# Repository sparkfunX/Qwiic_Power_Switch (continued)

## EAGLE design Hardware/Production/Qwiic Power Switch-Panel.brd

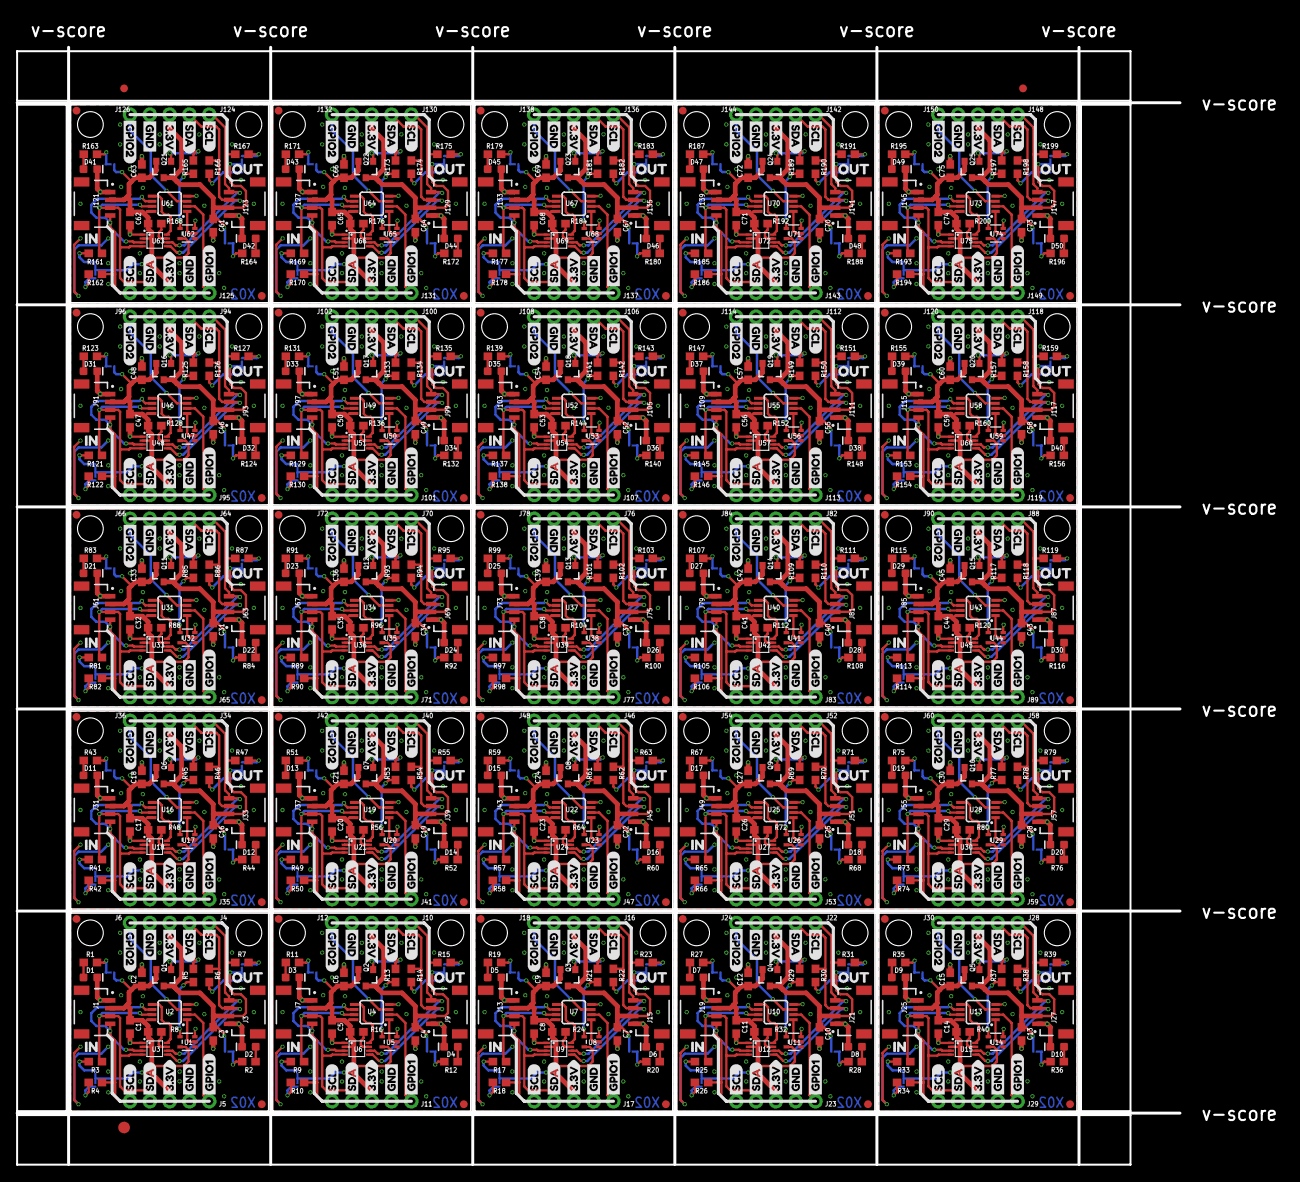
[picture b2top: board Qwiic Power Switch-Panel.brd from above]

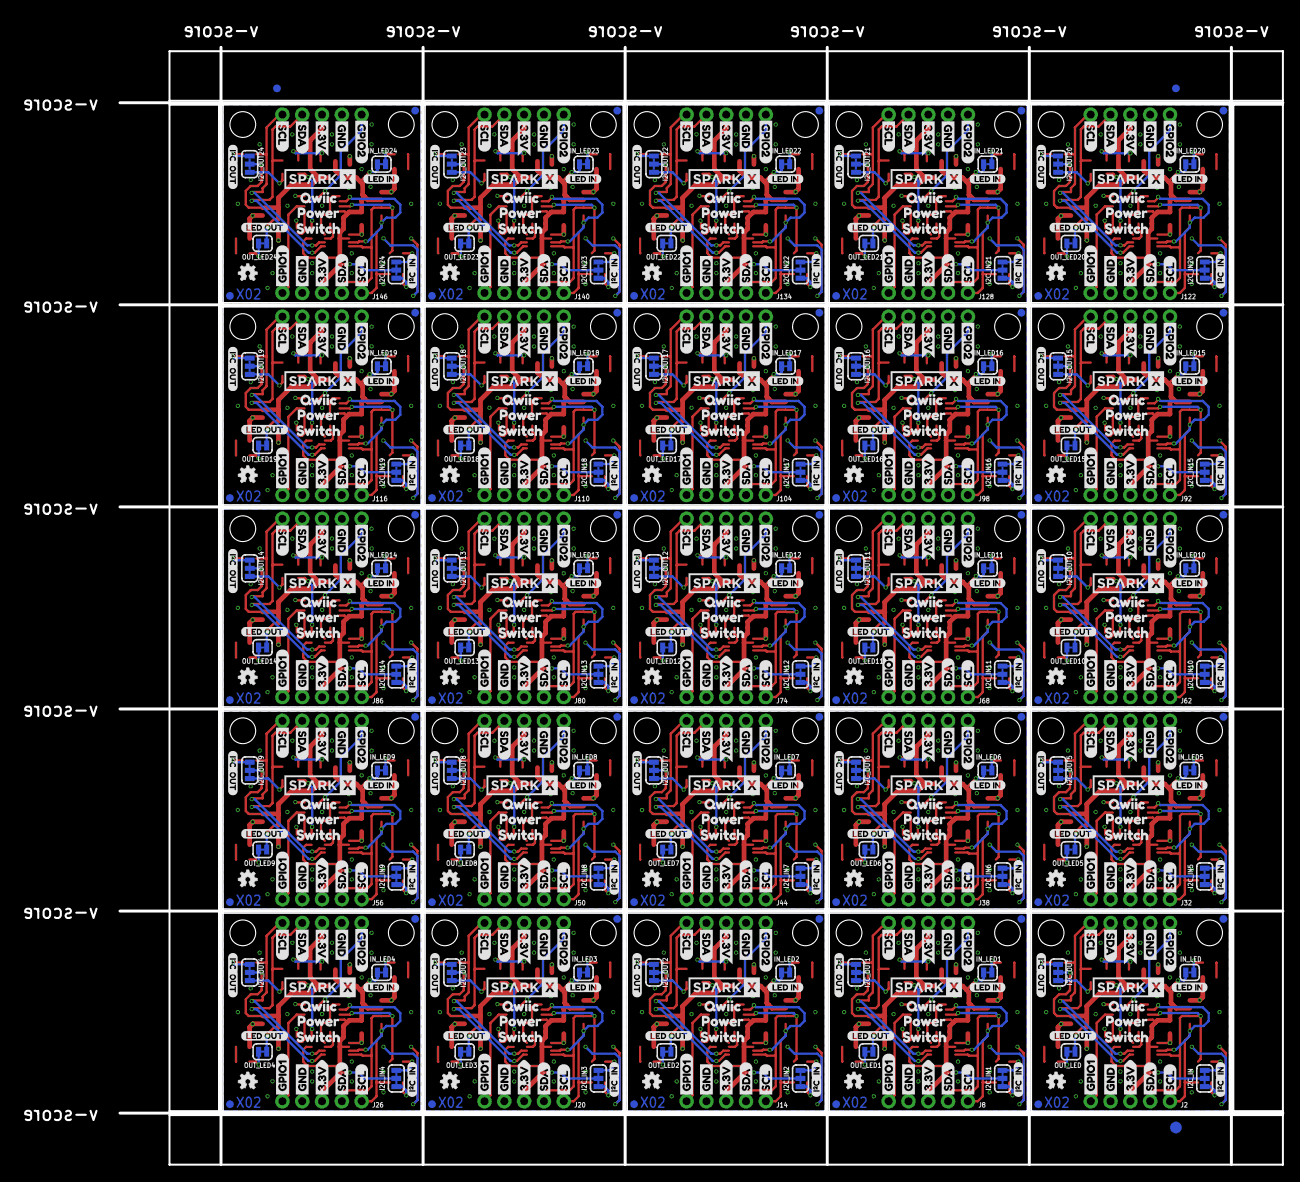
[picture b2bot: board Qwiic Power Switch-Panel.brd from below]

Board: 2 copper layers, 149.1 x 143.3 mm, 1656 parts (703 on the bottom side), 550 nets.

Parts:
C1, C3, C4, C5, C7, C8, C10, C11, C13, C14, C16, C17, C19, C20, C22, C23, C25, C26, C28, C29, C31, C32, C34, C35, C37, C38, C40, C41, C43, C44, C46, C47, C49, C50, C52, C53, C55, C56, C58, C59, C61, C62, C64, C65, C67, C68, C70, C71, C73, C74: 0.1uF; 0603
C2, C6, C9, C12, C15, C18, C21, C24, C27, C30, C33, C36, C39, C42, C45, C48, C51, C54, C57, C60, C63, C66, C69, C72, C75: 10uF; 0603
D1, D3, D5, D7, D9, D11, D13, D15, D17, D19, D21, D23, D25, D27, D29, D31, D33, D35, D37, D39, D41, D43, D45, D47, D49: RED; LED-0603
D2, D4, D6, D8, D10, D12, D14, D16, D18, D20, D22, D24, D26, D28, D30, D32, D34, D36, D38, D40, D42, D44, D46, D48, D50: GREEN; LED-0603
E$1, E$2, E$3, E$4: FIDUCIAL-1X2
E$5, E$6: FIDUCIAL-1.5X3
I2C_IN, I2C_IN1, I2C_IN2, I2C_IN3, I2C_IN4, I2C_IN5, I2C_IN6, I2C_IN7, I2C_IN8, I2C_IN9, I2C_IN10, I2C_IN11, I2C_IN12, I2C_IN13, I2C_IN14, I2C_IN15, I2C_IN16, I2C_IN17, I2C_IN18, I2C_IN19, I2C_IN20, I2C_IN21, I2C_IN22, I2C_IN23, I2C_IN24, I2C_OUT, I2C_OUT1, I2C_OUT2, I2C_OUT3, I2C_OUT4, I2C_OUT5, I2C_OUT6, I2C_OUT7, I2C_OUT8, I2C_OUT9, I2C_OUT10, I2C_OUT11, I2C_OUT12, I2C_OUT13, I2C_OUT14, I2C_OUT15, I2C_OUT16, I2C_OUT17, I2C_OUT18, I2C_OUT19, I2C_OUT20, I2C_OUT21, I2C_OUT22, I2C_OUT23, I2C_OUT24: JUMPER-SMT_3_2-NC_TRACE_SILK; SMT-JUMPER_3_2-NC_TRACE_SILK
IN_LED, IN_LED1, IN_LED2, IN_LED3, IN_LED4, IN_LED5, IN_LED6, IN_LED7, IN_LED8, IN_LED9, IN_LED10, IN_LED11, IN_LED12, IN_LED13, IN_LED14, IN_LED15, IN_LED16, IN_LED17, IN_LED18, IN_LED19, IN_LED20, IN_LED21, IN_LED22, IN_LED23, IN_LED24: IN_LED; SMT-JUMPER_2_NC_TRACE_SILK
J1, J3, J7, J9, J13, J15, J19, J21, J25, J27, J31, J33, J37, J39, J43, J45, J49, J51, J55, J57, J61, J63, J67, J69, J73, J75, J79, J81, J85, J87, J91, J93, J97, J99, J103, J105, J109, J111, J115, J117, J121, J123, J127, J129, J133, J135, J139, J141, J145, J147: Qwiic Right Angle; JST04_1MM_RA
J2, J4, J8, J10, J14, J16, J20, J22, J26, J28, J32, J34, J38, J40, J44, J46, J50, J52, J56, J58, J62, J64, J68, J70, J74, J76, J80, J82, J86, J88, J92, J94, J98, J100, J104, J106, J110, J112, J116, J118, J122, J124, J128, J130, J134, J136, J140, J142, J146, J148: PTH; 1X04_NO_SILK
J5, J6, J11, J12, J17, J18, J23, J24, J29, J30, J35, J36, J41, J42, J47, J48, J53, J54, J59, J60, J65, J66, J71, J72, J77, J78, J83, J84, J89, J90, J95, J96, J101, J102, J107, J108, J113, J114, J119, J120, J125, J126, J131, J132, J137, J138, J143, J144, J149, J150: 1X01_NO_SILK
JP1, JP2, JP5, JP6, JP9, JP10, JP11, JP12, JP15, JP16, JP17, JP18, JP21, JP22, JP23, JP24, JP27, JP28, JP29, JP30, JP33, JP34, JP35, JP36, JP39, JP40, JP41, JP42, JP45, JP46, JP47, JP48, JP51, JP52, JP53, JP54, JP57, JP58, JP59, JP60, JP63, JP64, JP65, JP66, JP69, JP70, JP71, JP72, JP75, JP76, JP77, JP78, JP81, JP82, JP83, JP84, JP87, JP88, JP89, JP90, JP93, JP94, JP95, JP96, JP99, JP100, JP101, JP102, JP105, JP106, JP107, JP108, JP111, JP112, JP113, JP114, JP117, JP118, JP119, JP120, JP123, JP124, JP125, JP126, JP129, JP130, JP131, JP132, JP135, JP136, JP137, JP138, JP141, JP142, JP143, JP144, JP147, JP148, JP149, JP150: FIDUCIAL1X2; FIDUCIAL-1X2
JP3, JP4, JP7, JP8, JP13, JP14, JP19, JP20, JP25, JP26, JP31, JP32, JP37, JP38, JP43, JP44, JP49, JP50, JP55, JP56, JP61, JP62, JP67, JP68, JP73, JP74, JP79, JP80, JP85, JP86, JP91, JP92, JP97, JP98, JP103, JP104, JP109, JP110, JP115, JP116, JP121, JP122, JP127, JP128, JP133, JP134, JP139, JP140, JP145, JP146: STAND-OFF
LOGO1, LOGO2, LOGO3, LOGO4, LOGO5, LOGO6, LOGO7, LOGO8, LOGO9, LOGO10, LOGO11, LOGO12, LOGO13, LOGO14, LOGO15, LOGO16, LOGO17, LOGO18, LOGO19, LOGO20, LOGO21, LOGO22, LOGO23, LOGO24, LOGO25: OSHW-LOGOMINI; OSHW-LOGO-MINI
OUT_LED, OUT_LED1, OUT_LED2, OUT_LED3, OUT_LED4, OUT_LED5, OUT_LED6, OUT_LED7, OUT_LED8, OUT_LED9, OUT_LED10, OUT_LED11, OUT_LED12, OUT_LED13, OUT_LED14, OUT_LED15, OUT_LED16, OUT_LED17, OUT_LED18, OUT_LED19, OUT_LED20, OUT_LED21, OUT_LED22, OUT_LED23, OUT_LED24: OUT_LED; SMT-JUMPER_2_NC_TRACE_SILK
Q1, Q2, Q3, Q4, Q5, Q6, Q7, Q8, Q9, Q10, Q11, Q12, Q13, Q14, Q15, Q16, Q17, Q18, Q19, Q20, Q21, Q22, Q23, Q24, Q25: 20V/4.2A/52mΩ/1.4W; SOT23-3
R1, R5, R11, R13, R19, R21, R27, R29, R35, R37, R43, R45, R51, R53, R59, R61, R67, R69, R75, R77, R83, R85, R91, R93, R99, R101, R107, R109, R115, R117, R123, R125, R131, R133, R139, R141, R147, R149, R155, R157, R163, R165, R171, R173, R179, R181, R187, R189, R195, R197: 1k; 0603
R2, R12, R20, R28, R36, R44, R52, R60, R68, R76, R84, R92, R100, R108, R116, R124, R132, R140, R148, R156, R164, R172, R180, R188, R196: 470; 0603
R3, R4, R6, R7, R9, R10, R14, R15, R17, R18, R22, R23, R25, R26, R30, R31, R33, R34, R38, R39, R41, R42, R46, R47, R49, R50, R54, R55, R57, R58, R62, R63, R65, R66, R70, R71, R73, R74, R78, R79, R81, R82, R86, R87, R89, R90, R94, R95, R97, R98, R102, R103, R105, R106, R110, R111, R113, R114, R118, R119, R121, R122, R126, R127, R129, R130, R134, R135, R137, R138, R142, R143, R145, R146, R150, R151, R153, R154, R158, R159, R161, R162, R166, R167, R169, R170, R174, R175, R177, R178, R182, R183, R185, R186, R190, R191, R193, R194, R198, R199: 2.2k; 0603
R8, R16, R24, R32, R40, R48, R56, R64, R72, R80, R88, R96, R104, R112, R120, R128, R136, R144, R152, R160, R168, R176, R184, R192, R200: 200k; 0603
U1, U5, U8, U11, U14, U17, U20, U23, U26, U29, U32, U35, U38, U41, U44, U47, U50, U53, U56, U59, U62, U65, U68, U71, U74: 74HC1G04; SOT353
U2, U4, U7, U10, U13, U16, U19, U22, U25, U28, U31, U34, U37, U40, U43, U46, U49, U52, U55, U58, U61, U64, U67, U70, U73: PCA9536; MSOP8
U3, U6, U9, U12, U15, U18, U21, U24, U27, U30, U33, U36, U39, U42, U45, U48, U51, U54, U57, U60, U63, U66, U69, U72, U75: VSSOP_8PIN
U$1, U$28, U$52, U$62, U$84, U$94, U$116, U$126, U$148, U$158, U$180, U$190, U$212, U$222, U$244, U$254, U$276, U$286, U$308, U$318, U$340, U$350, U$372, U$382, U$404, U$414, U$436, U$446, U$468, U$478, U$500, U$510, U$532, U$542, U$564, U$574, U$596, U$606, U$628, U$638, U$660, U$670, U$692, U$702, U$724, U$734, U$756, U$766, U$788, U$798: IN0
U$2, U$21, U$65, U$97, U$129, U$161, U$193, U$225, U$257, U$289, U$321, U$353, U$385, U$417, U$449, U$481, U$513, U$545, U$577, U$609, U$641, U$673, U$705, U$737, U$769: SPARKX-LOGO4; SPARKX-MEDIUM
U$3, U$8, U$13, U$22, U$33, U$37, U$41, U$44, U$66, U$69, U$73, U$76, U$98, U$101, U$105, U$108, U$130, U$133, U$137, U$140, U$162, U$165, U$169, U$172, U$194, U$197, U$201, U$204, U$226, U$229, U$233, U$236, U$258, U$261, U$265, U$268, U$290, U$293, U$297, U$300, U$322, U$325, U$329, U$332, U$354, U$357, U$361, U$364, U$386, U$389, U$393, U$396, U$418, U$421, U$425, U$428, U$450, U$453, U$457, U$460, U$482, U$485, U$489, U$492, U$514, U$517, U$521, U$524, U$546, U$549, U$553, U$556, U$578, U$581, U$585, U$588, U$610, U$613, U$617, U$620, U$642, U$645, U$649, U$652, U$674, U$677, U$681, U$684, U$706, U$709, U$713, U$716, U$738, U$741, U$745, U$748, U$770, U$773, U$777, U$780: GND1
U$4, U$7, U$12, U$23, U$48, U$49, U$60, U$61, U$80, U$81, U$92, U$93, U$112, U$113, U$124, U$125, U$144, U$145, U$156, U$157, U$176, U$177, U$188, U$189, U$208, U$209, U$220, U$221, U$240, U$241, U$252, U$253, U$272, U$273, U$284, U$285, U$304, U$305, U$316, U$317, U$336, U$337, U$348, U$349, U$368, U$369, U$380, U$381, U$400, U$401, U$412, U$413, U$432, U$433, U$444, U$445, U$464, U$465, U$476, U$477, U$496, U$497, U$508, U$509, U$528, U$529, U$540, U$541, U$560, U$561, U$572, U$573, U$592, U$593, U$604, U$605, U$624, U$625, U$636, U$637, U$656, U$657, U$668, U$669, U$688, U$689, U$700, U$701, U$720, U$721, U$732, U$733, U$752, U$753, U$764, U$765, U$784, U$785, U$796, U$797: 3#3V0
U$5, U$11, U$15, U$27, U$36, U$38, U$43, U$45, U$68, U$70, U$75, U$77, U$100, U$102, U$107, U$109, U$132, U$134, U$139, U$141, U$164, U$166, U$171, U$173, U$196, U$198, U$203, U$205, U$228, U$230, U$235, U$237, U$260, U$262, U$267, U$269, U$292, U$294, U$299, U$301, U$324, U$326, U$331, U$333, U$356, U$358, U$363, U$365, U$388, U$390, U$395, U$397, U$420, U$422, U$427, U$429, U$452, U$454, U$459, U$461, U$484, U$486, U$491, U$493, U$516, U$518, U$523, U$525, U$548, U$550, U$555, U$557, U$580, U$582, U$587, U$589, U$612, U$614, U$619, U$621, U$644, U$646, U$651, U$653, U$676, U$678, U$683, U$685, U$708, U$710, U$715, U$717, U$740, U$742, U$747, U$749, U$772, U$774, U$779, U$781: SDA8
U$6, U$9, U$17, U$26, U$35, U$39, U$42, U$46, U$67, U$71, U$74, U$78, U$99, U$103, U$106, U$110, U$131, U$135, U$138, U$142, U$163, U$167, U$170, U$174, U$195, U$199, U$202, U$206, U$227, U$231, U$234, U$238, U$259, U$263, U$266, U$270, U$291, U$295, U$298, U$302, U$323, U$327, U$330, U$334, U$355, U$359, U$362, U$366, U$387, U$391, U$394, U$398, U$419, U$423, U$426, U$430, U$451, U$455, U$458, U$462, U$483, U$487, U$490, U$494, U$515, U$519, U$522, U$526, U$547, U$551, U$554, U$558, U$579, U$583, U$586, U$590, U$611, U$615, U$618, U$622, U$643, U$647, U$650, U$654, U$675, U$679, U$682, U$686, U$707, U$711, U$714, U$718, U$739, U$743, U$746, U$750, U$771, U$775, U$778, U$782: SCL9
U$10, U$18, U$40, U$64, U$72, U$96, U$104, U$128, U$136, U$160, U$168, U$192, U$200, U$224, U$232, U$256, U$264, U$288, U$296, U$320, U$328, U$352, U$360, U$384, U$392, U$416, U$424, U$448, U$456, U$480, U$488, U$512, U$520, U$544, U$552, U$576, U$584, U$608, U$616, U$640, U$648, U$672, U$680, U$704, U$712, U$736, U$744, U$768, U$776, U$800: I_SUPER2_C-()-03
U$14, U$31, U$55, U$63, U$87, U$95, U$119, U$127, U$151, U$159, U$183, U$191, U$215, U$223, U$247, U$255, U$279, U$287, U$311, U$319, U$343, U$351, U$375, U$383, U$407, U$415, U$439, U$447, U$471, U$479, U$503, U$511, U$535, U$543, U$567, U$575, U$599, U$607, U$631, U$639, U$663, U$671, U$695, U$703, U$727, U$735, U$759, U$767, U$791, U$799: OUT0
U$16, U$24, U$50, U$58, U$82, U$90, U$114, U$122, U$146, U$154, U$178, U$186, U$210, U$218, U$242, U$250, U$274, U$282, U$306, U$314, U$338, U$346, U$370, U$378, U$402, U$410, U$434, U$442, U$466, U$474, U$498, U$506, U$530, U$538, U$562, U$570, U$594, U$602, U$626, U$634, U$658, U$666, U$690, U$698, U$722, U$730, U$754, U$762, U$786, U$794: GPIO10
U$19, U$47, U$79, U$111, U$143, U$175, U$207, U$239, U$271, U$303, U$335, U$367, U$399, U$431, U$463, U$495, U$527, U$559, U$591, U$623, U$655, U$687, U$719, U$751, U$783: QWIIC0
U$20, U$25, U$51, U$59, U$83, U$91, U$115, U$123, U$147, U$155, U$179, U$187, U$211, U$219, U$243, U$251, U$275, U$283, U$307, U$315, U$339, U$347, U$371, U$379, U$403, U$411, U$435, U$443, U$467, U$475, U$499, U$507, U$531, U$539, U$563, U$571, U$595, U$603, U$627, U$635, U$659, U$667, U$691, U$699, U$723, U$731, U$755, U$763, U$787, U$795: GPIO20
U$29, U$53, U$85, U$117, U$149, U$181, U$213, U$245, U$277, U$309, U$341, U$373, U$405, U$437, U$469, U$501, U$533, U$565, U$597, U$629, U$661, U$693, U$725, U$757, U$789: LED_IN0
U$30, U$54, U$86, U$118, U$150, U$182, U$214, U$246, U$278, U$310, U$342, U$374, U$406, U$438, U$470, U$502, U$534, U$566, U$598, U$630, U$662, U$694, U$726, U$758, U$790: LED_OUT0
U$32, U$56, U$88, U$120, U$152, U$184, U$216, U$248, U$280, U$312, U$344, U$376, U$408, U$440, U$472, U$504, U$536, U$568, U$600, U$632, U$664, U$696, U$728, U$760, U$792: POWER0
U$34, U$57, U$89, U$121, U$153, U$185, U$217, U$249, U$281, U$313, U$345, U$377, U$409, U$441, U$473, U$505, U$537, U$569, U$601, U$633, U$665, U$697, U$729, U$761, U$793: SWITCH0

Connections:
3.3V: C1.1, C2.1, I2C_IN.2, IN_LED.2, J1.2, J2.2, Q1.2, R8.2, U1.5, U2.8, U3.P2
3.3V1: C5.1, C6.1, I2C_IN1.2, IN_LED1.2, J7.2, J8.2, Q2.2, R16.2, U4.8, U5.5, U6.P2
3.3V2: C8.1, C9.1, I2C_IN2.2, IN_LED2.2, J13.2, J14.2, Q3.2, R24.2, U7.8, U8.5, U9.P2
3.3V3: C11.1, C12.1, I2C_IN3.2, IN_LED3.2, J19.2, J20.2, Q4.2, R32.2, U10.8, U11.5, U12.P2
3.3V4: C14.1, C15.1, I2C_IN4.2, IN_LED4.2, J25.2, J26.2, Q5.2, R40.2, U13.8, U14.5, U15.P2
3.3V5: C17.1, C18.1, I2C_IN5.2, IN_LED5.2, J31.2, J32.2, Q6.2, R48.2, U16.8, U17.5, U18.P2
3.3V6: C20.1, C21.1, I2C_IN6.2, IN_LED6.2, J37.2, J38.2, Q7.2, R56.2, U19.8, U20.5, U21.P2
3.3V7: C23.1, C24.1, I2C_IN7.2, IN_LED7.2, J43.2, J44.2, Q8.2, R64.2, U22.8, U23.5, U24.P2
3.3V8: C26.1, C27.1, I2C_IN8.2, IN_LED8.2, J49.2, J50.2, Q9.2, R72.2, U25.8, U26.5, U27.P2
3.3V9: C29.1, C30.1, I2C_IN9.2, IN_LED9.2, J55.2, J56.2, Q10.2, R80.2, U28.8, U29.5, U30.P2
3.3V10: C32.1, C33.1, I2C_IN10.2, IN_LED10.2, J61.2, J62.2, Q11.2, R88.2, U31.8, U32.5, U33.P2
3.3V11: C35.1, C36.1, I2C_IN11.2, IN_LED11.2, J67.2, J68.2, Q12.2, R96.2, U34.8, U35.5, U36.P2
3.3V12: C38.1, C39.1, I2C_IN12.2, IN_LED12.2, J73.2, J74.2, Q13.2, R104.2, U37.8, U38.5, U39.P2
3.3V13: C41.1, C42.1, I2C_IN13.2, IN_LED13.2, J79.2, J80.2, Q14.2, R112.2, U40.8, U41.5, U42.P2
3.3V14: C44.1, C45.1, I2C_IN14.2, IN_LED14.2, J85.2, J86.2, Q15.2, R120.2, U43.8, U44.5, U45.P2
3.3V15: C47.1, C48.1, I2C_IN15.2, IN_LED15.2, J91.2, J92.2, Q16.2, R128.2, U46.8, U47.5, U48.P2
3.3V16: C50.1, C51.1, I2C_IN16.2, IN_LED16.2, J97.2, J98.2, Q17.2, R136.2, U49.8, U50.5, U51.P2
3.3V17: C53.1, C54.1, I2C_IN17.2, IN_LED17.2, J103.2, J104.2, Q18.2, R144.2, U52.8, U53.5, U54.P2
3.3V18: C56.1, C57.1, I2C_IN18.2, IN_LED18.2, J109.2, J110.2, Q19.2, R152.2, U55.8, U56.5, U57.P2
3.3V19: C59.1, C60.1, I2C_IN19.2, IN_LED19.2, J115.2, J116.2, Q20.2, R160.2, U58.8, U59.5, U60.P2
3.3V20: C62.1, C63.1, I2C_IN20.2, IN_LED20.2, J121.2, J122.2, Q21.2, R168.2, U61.8, U62.5, U63.P2
3.3V21: C65.1, C66.1, I2C_IN21.2, IN_LED21.2, J127.2, J128.2, Q22.2, R176.2, U64.8, U65.5, U66.P2
3.3V22: C68.1, C69.1, I2C_IN22.2, IN_LED22.2, J133.2, J134.2, Q23.2, R184.2, U67.8, U68.5, U69.P2
3.3V23: C71.1, C72.1, I2C_IN23.2, IN_LED23.2, J139.2, J140.2, Q24.2, R192.2, U70.8, U71.5, U72.P2
3.3V24: C74.1, C75.1, I2C_IN24.2, IN_LED24.2, J145.2, J146.2, Q25.2, R200.2, U73.8, U74.5, U75.P2
GND: C1.2, C2.2, C3.2, D1.C, D2.C, J1.1, J2.1, J3.1, J4.1, U1.3, U2.4, U3.P1
GND1: C4.2, C5.2, C6.2, D3.C, D4.C, J7.1, J8.1, J9.1, J10.1, U4.4, U5.3, U6.P1
GND2: C7.2, C8.2, C9.2, D5.C, D6.C, J13.1, J14.1, J15.1, J16.1, U7.4, U8.3, U9.P1
GND3: C10.2, C11.2, C12.2, D7.C, D8.C, J19.1, J20.1, J21.1, J22.1, U10.4, U11.3, U12.P1
GND4: C13.2, C14.2, C15.2, D9.C, D10.C, J25.1, J26.1, J27.1, J28.1, U13.4, U14.3, U15.P1
GND5: C16.2, C17.2, C18.2, D11.C, D12.C, J31.1, J32.1, J33.1, J34.1, U16.4, U17.3, U18.P1
GND6: C19.2, C20.2, C21.2, D13.C, D14.C, J37.1, J38.1, J39.1, J40.1, U19.4, U20.3, U21.P1
GND7: C22.2, C23.2, C24.2, D15.C, D16.C, J43.1, J44.1, J45.1, J46.1, U22.4, U23.3, U24.P1
GND8: C25.2, C26.2, C27.2, D17.C, D18.C, J49.1, J50.1, J51.1, J52.1, U25.4, U26.3, U27.P1
GND9: C28.2, C29.2, C30.2, D19.C, D20.C, J55.1, J56.1, J57.1, J58.1, U28.4, U29.3, U30.P1
GND10: C31.2, C32.2, C33.2, D21.C, D22.C, J61.1, J62.1, J63.1, J64.1, U31.4, U32.3, U33.P1
GND11: C34.2, C35.2, C36.2, D23.C, D24.C, J67.1, J68.1, J69.1, J70.1, U34.4, U35.3, U36.P1
GND12: C37.2, C38.2, C39.2, D25.C, D26.C, J73.1, J74.1, J75.1, J76.1, U37.4, U38.3, U39.P1
GND13: C40.2, C41.2, C42.2, D27.C, D28.C, J79.1, J80.1, J81.1, J82.1, U40.4, U41.3, U42.P1
GND14: C43.2, C44.2, C45.2, D29.C, D30.C, J85.1, J86.1, J87.1, J88.1, U43.4, U44.3, U45.P1
GND15: C46.2, C47.2, C48.2, D31.C, D32.C, J91.1, J92.1, J93.1, J94.1, U46.4, U47.3, U48.P1
GND16: C49.2, C50.2, C51.2, D33.C, D34.C, J97.1, J98.1, J99.1, J100.1, U49.4, U50.3, U51.P1
GND17: C52.2, C53.2, C54.2, D35.C, D36.C, J103.1, J104.1, J105.1, J106.1, U52.4, U53.3, U54.P1
GND18: C55.2, C56.2, C57.2, D37.C, D38.C, J109.1, J110.1, J111.1, J112.1, U55.4, U56.3, U57.P1
GND19: C58.2, C59.2, C60.2, D39.C, D40.C, J115.1, J116.1, J117.1, J118.1, U58.4, U59.3, U60.P1
GND20: C61.2, C62.2, C63.2, D41.C, D42.C, J121.1, J122.1, J123.1, J124.1, U61.4, U62.3, U63.P1
GND21: C64.2, C65.2, C66.2, D43.C, D44.C, J127.1, J128.1, J129.1, J130.1, U64.4, U65.3, U66.P1
GND22: C67.2, C68.2, C69.2, D45.C, D46.C, J133.1, J134.1, J135.1, J136.1, U67.4, U68.3, U69.P1
GND23: C70.2, C71.2, C72.2, D47.C, D48.C, J139.1, J140.1, J141.1, J142.1, U70.4, U71.3, U72.P1
GND24: C73.2, C74.2, C75.2, D49.C, D50.C, J145.1, J146.1, J147.1, J148.1, U73.4, U74.3, U75.P1
GPIO0: U1.2, U2.1
GPIO1: J5.1, U2.2
GPIO2: J6.1, U2.3
GPIO3: U2.5, U3.P8
GPIO4: U4.1, U5.2
GPIO5: J11.1, U4.2
GPIO6: J12.1, U4.3
GPIO7: U4.5, U6.P8
GPIO8: U7.1, U8.2
GPIO9: J17.1, U7.2
GPIO10: J18.1, U7.3
GPIO11: U7.5, U9.P8
GPIO12: U10.1, U11.2
GPIO13: J23.1, U10.2
GPIO14: J24.1, U10.3
GPIO15: U10.5, U12.P8
GPIO16: U13.1, U14.2
GPIO17: J29.1, U13.2
GPIO18: J30.1, U13.3
GPIO19: U13.5, U15.P8
GPIO20: U16.1, U17.2
GPIO21: J35.1, U16.2
GPIO22: J36.1, U16.3
GPIO23: U16.5, U18.P8
GPIO24: U19.1, U20.2
GPIO25: J41.1, U19.2
GPIO26: J42.1, U19.3
GPIO27: U19.5, U21.P8
GPIO28: U22.1, U23.2
GPIO29: J47.1, U22.2
GPIO30: J48.1, U22.3
GPIO31: U22.5, U24.P8
GPIO32: U25.1, U26.2
GPIO33: J53.1, U25.2
GPIO34: J54.1, U25.3
GPIO35: U25.5, U27.P8
GPIO36: U28.1, U29.2
GPIO37: J59.1, U28.2
GPIO38: J60.1, U28.3
GPIO39: U28.5, U30.P8
GPIO40: U31.1, U32.2
GPIO41: J65.1, U31.2
GPIO42: J66.1, U31.3
GPIO43: U31.5, U33.P8
GPIO44: U34.1, U35.2
GPIO45: J71.1, U34.2
GPIO46: J72.1, U34.3
GPIO47: U34.5, U36.P8
GPIO48: U37.1, U38.2
GPIO49: J77.1, U37.2
GPIO50: J78.1, U37.3
GPIO51: U37.5, U39.P8
GPIO52: U40.1, U41.2
GPIO53: J83.1, U40.2
GPIO54: J84.1, U40.3
GPIO55: U40.5, U42.P8
GPIO56: U43.1, U44.2
GPIO57: J89.1, U43.2
GPIO58: J90.1, U43.3
GPIO59: U43.5, U45.P8
GPIO60: U46.1, U47.2
GPIO61: J95.1, U46.2
GPIO62: J96.1, U46.3
GPIO63: U46.5, U48.P8
GPIO64: U49.1, U50.2
GPIO65: J101.1, U49.2
GPIO66: J102.1, U49.3
GPIO67: U49.5, U51.P8
GPIO68: U52.1, U53.2
GPIO69: J107.1, U52.2
GPIO70: J108.1, U52.3
GPIO71: U52.5, U54.P8
GPIO72: U55.1, U56.2
GPIO73: J113.1, U55.2
GPIO74: J114.1, U55.3
GPIO75: U55.5, U57.P8
GPIO76: U58.1, U59.2
GPIO77: J119.1, U58.2
GPIO78: J120.1, U58.3
GPIO79: U58.5, U60.P8
GPIO80: U61.1, U62.2
GPIO81: J125.1, U61.2
GPIO82: J126.1, U61.3
GPIO83: U61.5, U63.P8
GPIO84: U64.1, U65.2
GPIO85: J131.1, U64.2
GPIO86: J132.1, U64.3
GPIO87: U64.5, U66.P8
GPIO88: U67.1, U68.2
GPIO89: J137.1, U67.2
GPIO90: J138.1, U67.3
GPIO91: U67.5, U69.P8
GPIO92: U70.1, U71.2
GPIO93: J143.1, U70.2
GPIO94: J144.1, U70.3
GPIO95: U70.5, U72.P8
GPIO96: U73.1, U74.2
GPIO97: J149.1, U73.2
GPIO98: J150.1, U73.3
GPIO99: U73.5, U75.P8
unnamed: I2C_IN.1, R4.2
unnamed: I2C_IN.3, R3.2
unnamed: D1.A, R1.1
unnamed: IN_LED.1, R1.2
unnamed: R5.1, U1.4
unnamed: Q1.1, R5.2
unnamed: OUT_LED.1, R2.2
unnamed: I2C_OUT.1, R7.2
unnamed: D2.A, R2.1
unnamed: I2C_OUT.3, R6.2
unnamed: I2C_IN1.1, R10.2
unnamed: R8.1, U3.P7
unnamed: I2C_IN1.3, R9.2
unnamed: D3.A, R11.1
unnamed: D4.A, R12.1
unnamed: IN_LED1.1, R11.2
unnamed: OUT_LED1.1, R12.2
unnamed: R13.1, U5.4
unnamed: Q2.1, R13.2
unnamed: I2C_OUT1.1, R15.2
unnamed: I2C_OUT1.3, R14.2
unnamed: R16.1, U6.P7
unnamed: I2C_IN2.1, R18.2
unnamed: I2C_IN2.3, R17.2
unnamed: D5.A, R19.1
unnamed: D6.A, R20.1
unnamed: IN_LED2.1, R19.2
unnamed: OUT_LED2.1, R20.2
unnamed: R21.1, U8.4
unnamed: Q3.1, R21.2
unnamed: I2C_OUT2.1, R23.2
unnamed: I2C_OUT2.3, R22.2
unnamed: R24.1, U9.P7
unnamed: I2C_IN3.1, R26.2
unnamed: I2C_IN3.3, R25.2
unnamed: D7.A, R27.1
unnamed: D8.A, R28.1
unnamed: IN_LED3.1, R27.2
unnamed: OUT_LED3.1, R28.2
unnamed: R29.1, U11.4
unnamed: Q4.1, R29.2
unnamed: I2C_OUT3.1, R31.2
unnamed: I2C_OUT3.3, R30.2
unnamed: R32.1, U12.P7
unnamed: I2C_IN4.1, R34.2
unnamed: I2C_IN4.3, R33.2
unnamed: D9.A, R35.1
unnamed: D10.A, R36.1
unnamed: IN_LED4.1, R35.2
unnamed: OUT_LED4.1, R36.2
unnamed: R37.1, U14.4
unnamed: Q5.1, R37.2
unnamed: I2C_OUT4.1, R39.2
unnamed: I2C_OUT4.3, R38.2
unnamed: R40.1, U15.P7
unnamed: I2C_IN5.1, R42.2
unnamed: I2C_IN5.3, R41.2
unnamed: D11.A, R43.1
unnamed: D12.A, R44.1
unnamed: IN_LED5.1, R43.2
unnamed: OUT_LED5.1, R44.2
unnamed: R45.1, U17.4
unnamed: Q6.1, R45.2
unnamed: I2C_OUT5.1, R47.2
unnamed: I2C_OUT5.3, R46.2
unnamed: R48.1, U18.P7
unnamed: I2C_IN6.1, R50.2
unnamed: I2C_IN6.3, R49.2
unnamed: D13.A, R51.1
unnamed: D14.A, R52.1
unnamed: IN_LED6.1, R51.2
unnamed: OUT_LED6.1, R52.2
unnamed: R53.1, U20.4
unnamed: Q7.1, R53.2
unnamed: I2C_OUT6.1, R55.2
unnamed: I2C_OUT6.3, R54.2
unnamed: R56.1, U21.P7
unnamed: I2C_IN7.1, R58.2
unnamed: I2C_IN7.3, R57.2
unnamed: D15.A, R59.1
unnamed: D16.A, R60.1
unnamed: IN_LED7.1, R59.2
unnamed: OUT_LED7.1, R60.2
unnamed: R61.1, U23.4
unnamed: Q8.1, R61.2
unnamed: I2C_OUT7.1, R63.2
unnamed: I2C_OUT7.3, R62.2
unnamed: R64.1, U24.P7
unnamed: I2C_IN8.1, R66.2
unnamed: I2C_IN8.3, R65.2
unnamed: D17.A, R67.1
unnamed: D18.A, R68.1
unnamed: IN_LED8.1, R67.2
unnamed: OUT_LED8.1, R68.2
unnamed: R69.1, U26.4
unnamed: Q9.1, R69.2
unnamed: I2C_OUT8.1, R71.2
unnamed: I2C_OUT8.3, R70.2
unnamed: R72.1, U27.P7
unnamed: I2C_IN9.1, R74.2
unnamed: I2C_IN9.3, R73.2
unnamed: D19.A, R75.1
unnamed: D20.A, R76.1
unnamed: IN_LED9.1, R75.2
unnamed: OUT_LED9.1, R76.2
unnamed: R77.1, U29.4
unnamed: Q10.1, R77.2
unnamed: I2C_OUT9.1, R79.2
unnamed: I2C_OUT9.3, R78.2
unnamed: R80.1, U30.P7
unnamed: I2C_IN10.1, R82.2
unnamed: I2C_IN10.3, R81.2
unnamed: D21.A, R83.1
unnamed: D22.A, R84.1
unnamed: IN_LED10.1, R83.2
unnamed: OUT_LED10.1, R84.2
unnamed: R85.1, U32.4
unnamed: Q11.1, R85.2
unnamed: I2C_OUT10.1, R87.2
unnamed: I2C_OUT10.3, R86.2
unnamed: R88.1, U33.P7
unnamed: I2C_IN11.1, R90.2
unnamed: I2C_IN11.3, R89.2
unnamed: D23.A, R91.1
unnamed: D24.A, R92.1
unnamed: IN_LED11.1, R91.2
unnamed: OUT_LED11.1, R92.2
unnamed: R93.1, U35.4
unnamed: Q12.1, R93.2
unnamed: I2C_OUT11.1, R95.2
unnamed: I2C_OUT11.3, R94.2
unnamed: R96.1, U36.P7
unnamed: I2C_IN12.1, R98.2
unnamed: I2C_IN12.3, R97.2
unnamed: D25.A, R99.1
unnamed: D26.A, R100.1
unnamed: IN_LED12.1, R99.2
unnamed: OUT_LED12.1, R100.2
unnamed: R101.1, U38.4
unnamed: Q13.1, R101.2
unnamed: I2C_OUT12.1, R103.2
unnamed: I2C_OUT12.3, R102.2
unnamed: R104.1, U39.P7
unnamed: I2C_IN13.1, R106.2
unnamed: I2C_IN13.3, R105.2
unnamed: D27.A, R107.1
unnamed: D28.A, R108.1
unnamed: IN_LED13.1, R107.2
unnamed: OUT_LED13.1, R108.2
unnamed: R109.1, U41.4
unnamed: Q14.1, R109.2
unnamed: I2C_OUT13.1, R111.2
unnamed: I2C_OUT13.3, R110.2
unnamed: R112.1, U42.P7
unnamed: I2C_IN14.1, R114.2
unnamed: I2C_IN14.3, R113.2
unnamed: D29.A, R115.1
unnamed: D30.A, R116.1
unnamed: IN_LED14.1, R115.2
unnamed: OUT_LED14.1, R116.2
unnamed: R117.1, U44.4
unnamed: Q15.1, R117.2
unnamed: I2C_OUT14.1, R119.2
unnamed: I2C_OUT14.3, R118.2
unnamed: R120.1, U45.P7
unnamed: I2C_IN15.1, R122.2
unnamed: I2C_IN15.3, R121.2
unnamed: D31.A, R123.1
unnamed: D32.A, R124.1
unnamed: IN_LED15.1, R123.2
unnamed: OUT_LED15.1, R124.2
unnamed: R125.1, U47.4
unnamed: Q16.1, R125.2
unnamed: I2C_OUT15.1, R127.2
unnamed: I2C_OUT15.3, R126.2
unnamed: R128.1, U48.P7
unnamed: I2C_IN16.1, R130.2
unnamed: I2C_IN16.3, R129.2
unnamed: D33.A, R131.1
unnamed: D34.A, R132.1
unnamed: IN_LED16.1, R131.2
unnamed: OUT_LED16.1, R132.2
unnamed: R133.1, U50.4
unnamed: Q17.1, R133.2
unnamed: I2C_OUT16.1, R135.2
unnamed: I2C_OUT16.3, R134.2
unnamed: R136.1, U51.P7
unnamed: I2C_IN17.1, R138.2
unnamed: I2C_IN17.3, R137.2
unnamed: D35.A, R139.1
unnamed: D36.A, R140.1
unnamed: IN_LED17.1, R139.2
unnamed: OUT_LED17.1, R140.2
unnamed: R141.1, U53.4
unnamed: Q18.1, R141.2
unnamed: I2C_OUT17.1, R143.2
unnamed: I2C_OUT17.3, R142.2
unnamed: R144.1, U54.P7
unnamed: I2C_IN18.1, R146.2
unnamed: I2C_IN18.3, R145.2
unnamed: D37.A, R147.1
unnamed: D38.A, R148.1
unnamed: IN_LED18.1, R147.2
unnamed: OUT_LED18.1, R148.2
unnamed: R149.1, U56.4
unnamed: Q19.1, R149.2
unnamed: I2C_OUT18.1, R151.2
unnamed: I2C_OUT18.3, R150.2
unnamed: R152.1, U57.P7
unnamed: I2C_IN19.1, R154.2
unnamed: I2C_IN19.3, R153.2
unnamed: D39.A, R155.1
unnamed: D40.A, R156.1
unnamed: IN_LED19.1, R155.2
unnamed: OUT_LED19.1, R156.2
unnamed: R157.1, U59.4
unnamed: Q20.1, R157.2
unnamed: I2C_OUT19.1, R159.2
unnamed: I2C_OUT19.3, R158.2
unnamed: R160.1, U60.P7
unnamed: I2C_IN20.1, R162.2
unnamed: I2C_IN20.3, R161.2
unnamed: D41.A, R163.1
unnamed: D42.A, R164.1
unnamed: IN_LED20.1, R163.2
unnamed: OUT_LED20.1, R164.2
unnamed: R165.1, U62.4
unnamed: Q21.1, R165.2
unnamed: I2C_OUT20.1, R167.2
unnamed: I2C_OUT20.3, R166.2
unnamed: R168.1, U63.P7
unnamed: I2C_IN21.1, R170.2
unnamed: I2C_IN21.3, R169.2
unnamed: D43.A, R171.1
unnamed: D44.A, R172.1
unnamed: IN_LED21.1, R171.2
unnamed: OUT_LED21.1, R172.2
unnamed: R173.1, U65.4
unnamed: Q22.1, R173.2
unnamed: I2C_OUT21.1, R175.2
unnamed: I2C_OUT21.3, R174.2
unnamed: R176.1, U66.P7
unnamed: I2C_IN22.1, R178.2
unnamed: I2C_IN22.3, R177.2
unnamed: D45.A, R179.1
unnamed: D46.A, R180.1
unnamed: IN_LED22.1, R179.2
unnamed: OUT_LED22.1, R180.2
unnamed: R181.1, U68.4
unnamed: Q23.1, R181.2
unnamed: I2C_OUT22.1, R183.2
unnamed: I2C_OUT22.3, R182.2
unnamed: R184.1, U69.P7
unnamed: I2C_IN23.1, R186.2
unnamed: I2C_IN23.3, R185.2
unnamed: D47.A, R187.1
unnamed: D48.A, R188.1
unnamed: IN_LED23.1, R187.2
unnamed: OUT_LED23.1, R188.2
unnamed: R189.1, U71.4
unnamed: Q24.1, R189.2
unnamed: I2C_OUT23.1, R191.2
unnamed: I2C_OUT23.3, R190.2
unnamed: R192.1, U72.P7
unnamed: I2C_IN24.1, R194.2
unnamed: I2C_IN24.3, R193.2
unnamed: D49.A, R195.1
unnamed: D50.A, R196.1
unnamed: IN_LED24.1, R195.2
unnamed: OUT_LED24.1, R196.2
unnamed: R197.1, U74.4
unnamed: Q25.1, R197.2
unnamed: I2C_OUT24.1, R199.2
unnamed: I2C_OUT24.3, R198.2
unnamed: R200.1, U75.P7
SCL: J1.4, J2.4, R4.1, U2.6, U3.P3
SCL1: J7.4, J8.4, R10.1, U4.6, U6.P3
SCL2: J13.4, J14.4, R18.1, U7.6, U9.P3
SCL3: J19.4, J20.4, R26.1, U10.6, U12.P3
SCL4: J25.4, J26.4, R34.1, U13.6, U15.P3
SCL5: J31.4, J32.4, R42.1, U16.6, U18.P3
SCL6: J37.4, J38.4, R50.1, U19.6, U21.P3
SCL7: J43.4, J44.4, R58.1, U22.6, U24.P3
SCL8: J49.4, J50.4, R66.1, U25.6, U27.P3
SCL9: J55.4, J56.4, R74.1, U28.6, U30.P3
SCL10: J61.4, J62.4, R82.1, U31.6, U33.P3
SCL11: J67.4, J68.4, R90.1, U34.6, U36.P3
SCL12: J73.4, J74.4, R98.1, U37.6, U39.P3
SCL13: J79.4, J80.4, R106.1, U40.6, U42.P3
SCL14: J85.4, J86.4, R114.1, U43.6, U45.P3
SCL15: J91.4, J92.4, R122.1, U46.6, U48.P3
SCL16: J97.4, J98.4, R130.1, U49.6, U51.P3
SCL17: J103.4, J104.4, R138.1, U52.6, U54.P3
SCL18: J109.4, J110.4, R146.1, U55.6, U57.P3
SCL19: J115.4, J116.4, R154.1, U58.6, U60.P3
SCL20: J121.4, J122.4, R162.1, U61.6, U63.P3
SCL21: J127.4, J128.4, R170.1, U64.6, U66.P3
SCL22: J133.4, J134.4, R178.1, U67.6, U69.P3
SCL23: J139.4, J140.4, R186.1, U70.6, U72.P3
SCL24: J145.4, J146.4, R194.1, U73.6, U75.P3
SCL_OUT: J3.4, J4.4, R7.1, U3.P6
SCL_OUT1: J9.4, J10.4, R15.1, U6.P6
SCL_OUT2: J15.4, J16.4, R23.1, U9.P6
SCL_OUT3: J21.4, J22.4, R31.1, U12.P6
SCL_OUT4: J27.4, J28.4, R39.1, U15.P6
SCL_OUT5: J33.4, J34.4, R47.1, U18.P6
SCL_OUT6: J39.4, J40.4, R55.1, U21.P6
SCL_OUT7: J45.4, J46.4, R63.1, U24.P6
SCL_OUT8: J51.4, J52.4, R71.1, U27.P6
SCL_OUT9: J57.4, J58.4, R79.1, U30.P6
SCL_OUT10: J63.4, J64.4, R87.1, U33.P6
SCL_OUT11: J69.4, J70.4, R95.1, U36.P6
SCL_OUT12: J75.4, J76.4, R103.1, U39.P6
SCL_OUT13: J81.4, J82.4, R111.1, U42.P6
SCL_OUT14: J87.4, J88.4, R119.1, U45.P6
SCL_OUT15: J93.4, J94.4, R127.1, U48.P6
SCL_OUT16: J99.4, J100.4, R135.1, U51.P6
SCL_OUT17: J105.4, J106.4, R143.1, U54.P6
SCL_OUT18: J111.4, J112.4, R151.1, U57.P6
SCL_OUT19: J117.4, J118.4, R159.1, U60.P6
SCL_OUT20: J123.4, J124.4, R167.1, U63.P6
SCL_OUT21: J129.4, J130.4, R175.1, U66.P6
SCL_OUT22: J135.4, J136.4, R183.1, U69.P6
SCL_OUT23: J141.4, J142.4, R191.1, U72.P6
SCL_OUT24: J147.4, J148.4, R199.1, U75.P6
SDA: J1.3, J2.3, R3.1, U2.7, U3.P4
SDA1: J7.3, J8.3, R9.1, U4.7, U6.P4
SDA2: J13.3, J14.3, R17.1, U7.7, U9.P4
SDA3: J19.3, J20.3, R25.1, U10.7, U12.P4
SDA4: J25.3, J26.3, R33.1, U13.7, U15.P4
SDA5: J31.3, J32.3, R41.1, U16.7, U18.P4
SDA6: J37.3, J38.3, R49.1, U19.7, U21.P4
SDA7: J43.3, J44.3, R57.1, U22.7, U24.P4
SDA8: J49.3, J50.3, R65.1, U25.7, U27.P4
SDA9: J55.3, J56.3, R73.1, U28.7, U30.P4
SDA10: J61.3, J62.3, R81.1, U31.7, U33.P4
SDA11: J67.3, J68.3, R89.1, U34.7, U36.P4
SDA12: J73.3, J74.3, R97.1, U37.7, U39.P4
SDA13: J79.3, J80.3, R105.1, U40.7, U42.P4
SDA14: J85.3, J86.3, R113.1, U43.7, U45.P4
SDA15: J91.3, J92.3, R121.1, U46.7, U48.P4
SDA16: J97.3, J98.3, R129.1, U49.7, U51.P4
SDA17: J103.3, J104.3, R137.1, U52.7, U54.P4
SDA18: J109.3, J110.3, R145.1, U55.7, U57.P4
SDA19: J115.3, J116.3, R153.1, U58.7, U60.P4
SDA20: J121.3, J122.3, R161.1, U61.7, U63.P4
SDA21: J127.3, J128.3, R169.1, U64.7, U66.P4
SDA22: J133.3, J134.3, R177.1, U67.7, U69.P4
SDA23: J139.3, J140.3, R185.1, U70.7, U72.P4
SDA24: J145.3, J146.3, R193.1, U73.7, U75.P4
SDA_OUT: J3.3, J4.3, R6.1, U3.P5
SDA_OUT1: J9.3, J10.3, R14.1, U6.P5
SDA_OUT2: J15.3, J16.3, R22.1, U9.P5
SDA_OUT3: J21.3, J22.3, R30.1, U12.P5
SDA_OUT4: J27.3, J28.3, R38.1, U15.P5
SDA_OUT5: J33.3, J34.3, R46.1, U18.P5
SDA_OUT6: J39.3, J40.3, R54.1, U21.P5
SDA_OUT7: J45.3, J46.3, R62.1, U24.P5
SDA_OUT8: J51.3, J52.3, R70.1, U27.P5
SDA_OUT9: J57.3, J58.3, R78.1, U30.P5
SDA_OUT10: J63.3, J64.3, R86.1, U33.P5
SDA_OUT11: J69.3, J70.3, R94.1, U36.P5
SDA_OUT12: J75.3, J76.3, R102.1, U39.P5
SDA_OUT13: J81.3, J82.3, R110.1, U42.P5
SDA_OUT14: J87.3, J88.3, R118.1, U45.P5
SDA_OUT15: J93.3, J94.3, R126.1, U48.P5
SDA_OUT16: J99.3, J100.3, R134.1, U51.P5
SDA_OUT17: J105.3, J106.3, R142.1, U54.P5
SDA_OUT18: J111.3, J112.3, R150.1, U57.P5
SDA_OUT19: J117.3, J118.3, R158.1, U60.P5
SDA_OUT20: J123.3, J124.3, R166.1, U63.P5
SDA_OUT21: J129.3, J130.3, R174.1, U66.P5
SDA_OUT22: J135.3, J136.3, R182.1, U69.P5
SDA_OUT23: J141.3, J142.3, R190.1, U72.P5
SDA_OUT24: J147.3, J148.3, R198.1, U75.P5
VOUT: C3.1, I2C_OUT.2, J3.2, J4.2, OUT_LED.2, Q1.3
VOUT1: C4.1, I2C_OUT1.2, J9.2, J10.2, OUT_LED1.2, Q2.3
VOUT2: C7.1, I2C_OUT2.2, J15.2, J16.2, OUT_LED2.2, Q3.3
VOUT3: C10.1, I2C_OUT3.2, J21.2, J22.2, OUT_LED3.2, Q4.3
VOUT4: C13.1, I2C_OUT4.2, J27.2, J28.2, OUT_LED4.2, Q5.3
VOUT5: C16.1, I2C_OUT5.2, J33.2, J34.2, OUT_LED5.2, Q6.3
VOUT6: C19.1, I2C_OUT6.2, J39.2, J40.2, OUT_LED6.2, Q7.3
VOUT7: C22.1, I2C_OUT7.2, J45.2, J46.2, OUT_LED7.2, Q8.3
VOUT8: C25.1, I2C_OUT8.2, J51.2, J52.2, OUT_LED8.2, Q9.3
VOUT9: C28.1, I2C_OUT9.2, J57.2, J58.2, OUT_LED9.2, Q10.3
VOUT10: C31.1, I2C_OUT10.2, J63.2, J64.2, OUT_LED10.2, Q11.3
VOUT11: C34.1, I2C_OUT11.2, J69.2, J70.2, OUT_LED11.2, Q12.3
VOUT12: C37.1, I2C_OUT12.2, J75.2, J76.2, OUT_LED12.2, Q13.3
VOUT13: C40.1, I2C_OUT13.2, J81.2, J82.2, OUT_LED13.2, Q14.3
VOUT14: C43.1, I2C_OUT14.2, J87.2, J88.2, OUT_LED14.2, Q15.3
VOUT15: C46.1, I2C_OUT15.2, J93.2, J94.2, OUT_LED15.2, Q16.3
VOUT16: C49.1, I2C_OUT16.2, J99.2, J100.2, OUT_LED16.2, Q17.3
VOUT17: C52.1, I2C_OUT17.2, J105.2, J106.2, OUT_LED17.2, Q18.3
VOUT18: C55.1, I2C_OUT18.2, J111.2, J112.2, OUT_LED18.2, Q19.3
VOUT19: C58.1, I2C_OUT19.2, J117.2, J118.2, OUT_LED19.2, Q20.3
VOUT20: C61.1, I2C_OUT20.2, J123.2, J124.2, OUT_LED20.2, Q21.3
VOUT21: C64.1, I2C_OUT21.2, J129.2, J130.2, OUT_LED21.2, Q22.3
VOUT22: C67.1, I2C_OUT22.2, J135.2, J136.2, OUT_LED22.2, Q23.3
VOUT23: C70.1, I2C_OUT23.2, J141.2, J142.2, OUT_LED23.2, Q24.3
VOUT24: C73.1, I2C_OUT24.2, J147.2, J148.2, OUT_LED24.2, Q25.3

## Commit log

2020-04-24 Finishing touches...
2020-05-13 sparkfun link corrections
2020-05-17 Version X02
2020-05-17 Updated the Library link
2020-05-18 Add x01 panel files
2020-05-18 Not quite finished - need to add the PCA9306 tPlace outline
2020-05-19 X02 ready for manufacture
2020-05-19 Add x02 production files
2020-06-18 Added the datasheets
2020-06-26 Update README.md
    This repo will be moving over to SparkFunX soon!
2021-11-01 Remove New_Parts.lbr
2021-11-01 Update panel dimensions
2021-11-01 Update README and LICENSE
